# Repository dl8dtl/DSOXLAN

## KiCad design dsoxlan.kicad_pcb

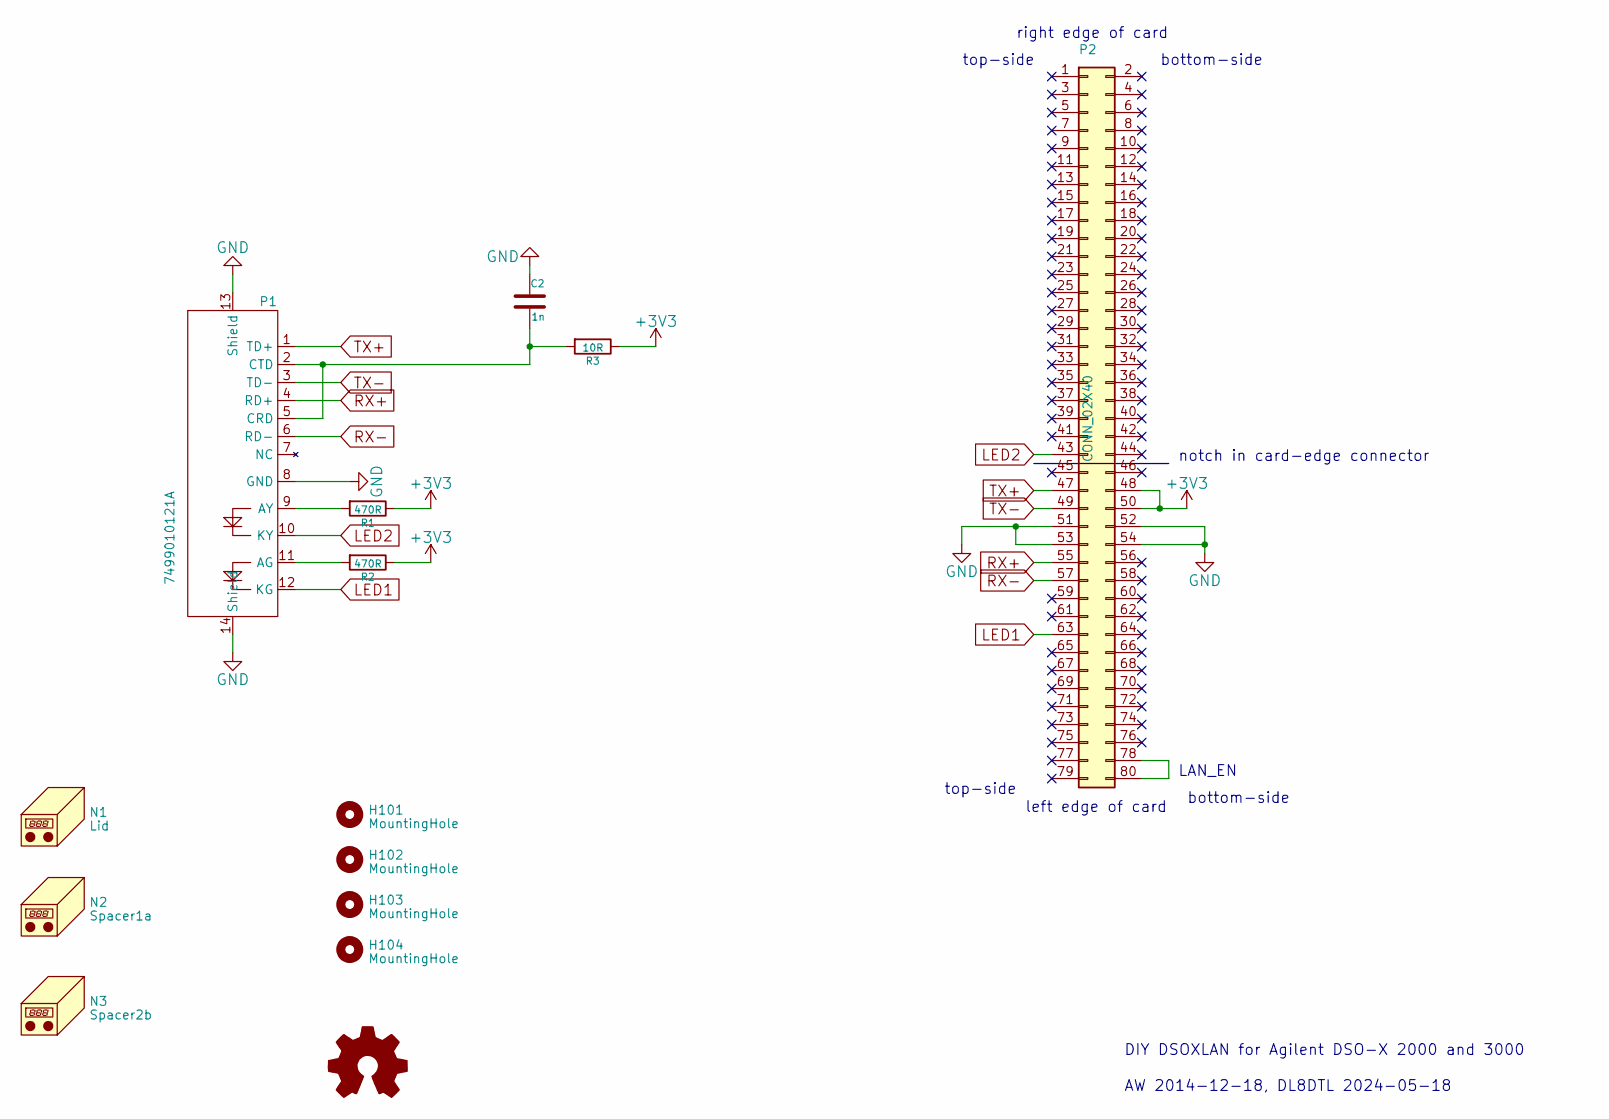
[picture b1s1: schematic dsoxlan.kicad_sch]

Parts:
C2: 1n; C_0805_2012Metric_Pad1.18x1.45mm_HandSolder
H101, H102, H103, H104: MountingHole; MountingHole_3.2mm_M3_ISO7380
N1: Lid
N2: Spacer1a
N3: Spacer2b
P1: 7499010121A; 7499011121A
P2: CONN_02X40; cardedge_40x2
R1, R2: 470R; R_0805_2012Metric_Pad1.20x1.40mm_HandSolder
R3: 10R; R_0805_2012Metric_Pad1.20x1.40mm_HandSolder
SYM101: Logo_Open_Hardware_Small; OSHW-Symbol_6.7x6mm_Copper

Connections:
+3.3V: P2.48, P2.50, R1.1, R2.1, R3.1
GND: C2.1, P1.8 (GND), P1.13 (Shield), P1.14 (Shield), P2.51, P2.52, P2.53, P2.54
LED1: P1.12 (KG), P2.63
LED2: P1.10 (KY), P2.43
unnamed: P1.11 (AG), R2.2
unnamed: P1.9 (AY), R1.2
unnamed: C2.2, P1.2 (CTD), P1.5 (CRD), R3.2
unnamed: P2.78, P2.80
RX+: P1.4 (RD+), P2.55
RX-: P1.6 (RD-), P2.57
TX+: P1.1 (TD+), P2.47
TX-: P1.3 (TD-), P2.49

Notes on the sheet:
bottom-side
top-side
left edge of card
DIY DSOXLAN for Agilent DSO-X 2000 and 3000
AW 2014-12-18, DL8DTL 2024-05-18
right edge of card
notch in card-edge connector
LAN_EN

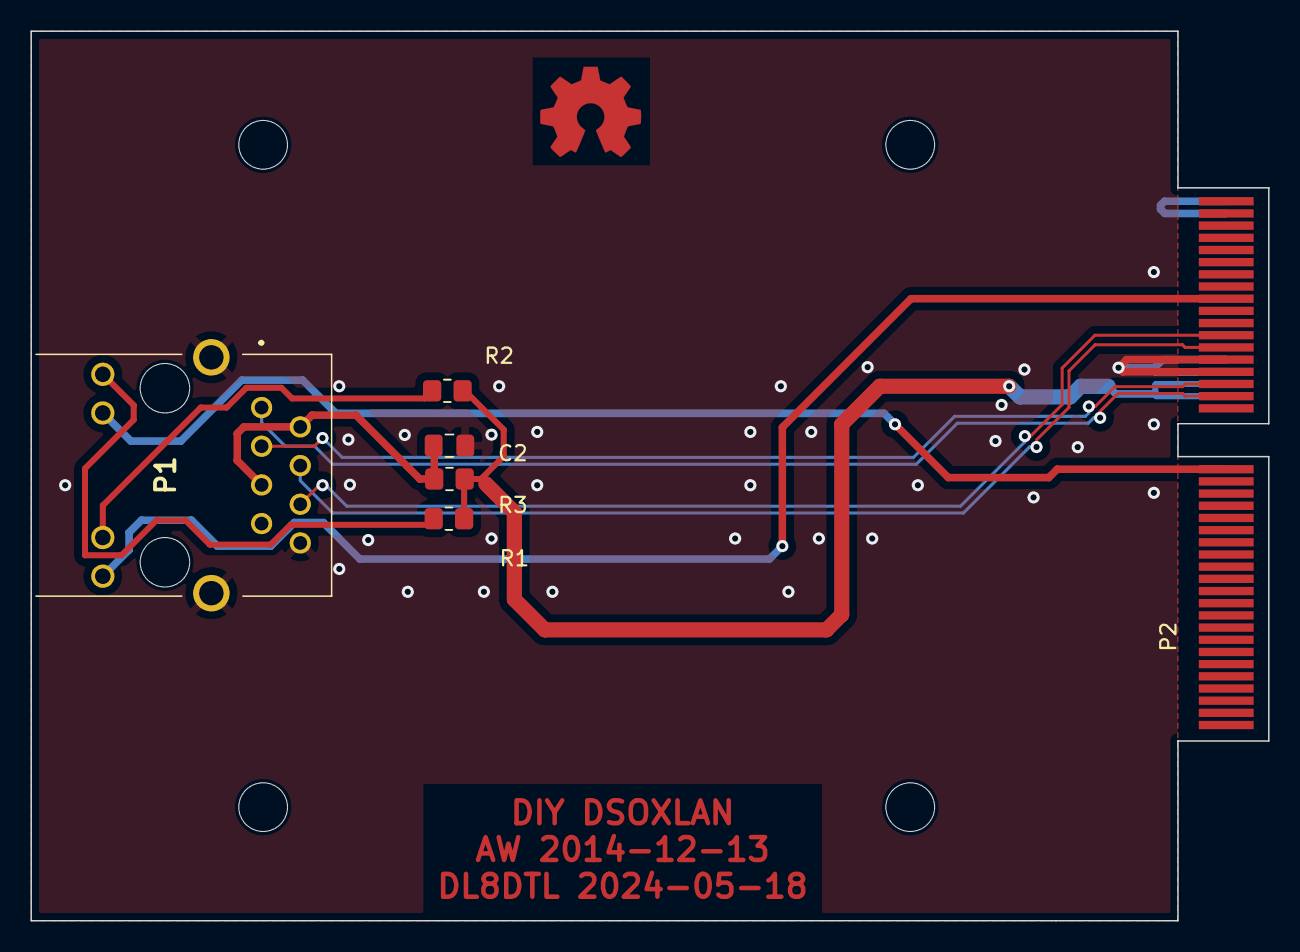
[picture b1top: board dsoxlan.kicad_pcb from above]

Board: 2 copper layers, 81.3 x 58.4 mm, 14 parts (1 on the bottom side), 12 nets.

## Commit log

2024-05-24 Add Würth 7499011121A
    This part slightly differs from the 7499010121A, but offers the
    same functionality.
2024-05-24 Replace 7499010121A by 7499011121A
2024-05-24 Symbol for WE7499011121A
2024-05-24 Regenerate gerbers
2024-05-24 Add the housing parts to schematics
    This allows to assign them correct reference designators, and
    removes the DRC warnings about schematic parity mismatches.
2024-05-24 Update Gerber data
